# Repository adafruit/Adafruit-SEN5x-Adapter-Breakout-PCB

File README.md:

## Adafruit SEN54 or SEN55 Adapter Breakout - STEMMA QT / Qwiic PCB

<a href="http://www.adafruit.com/products/5964"><br/>
Click here to purchase one from the Adafruit shop</a>

PCB files for the Adafruit SEN54 or SEN55 Adapter Breakout - STEMMA QT / Qwiic. 

Format is EagleCAD schematic and board layout
* https://www.adafruit.com/product/5964

### Description

Now you can quickly integrate the Sensirion SEN54 / SEN55 environmental sensor node into your microcontroller or microcomputer project, with no soldering or fiddly breadboarding - thanks to this here Adafruit SEN54 or SEN55 Adapter Breakout. We covered the awesome Sensirion SEN54 / SEN55 environmental sensor nodes on EYE ON NPI a while ago, it's an awesome all-in-one air quality sensor, but has the annoyance that it requires 5V power and it has a special cable connection.

This adapter breakout will make an instant friendship with all SEN5x boards, thanks to a JST GH-compatible connector in the middle so that you can plug a 6-pin GH cable directly between your SEN and this adapter. In the middle is a small switch-cap boost converter that will generate 5V at 100mA to power the fan and electronics in the SEN5x even if you're using 3V power and logic. Then you can use any ol' STEMMA QT cable to plug into your Metro, Feather, QT Py, Raspberry Pi, etc etc. I2C port.

Once you've got it plugged together, you can run Sensirion's Arduino library or Raspberry Pi Python library to read temperature, humidity, VOC, Particulate Matter PM1 / PM2.5 / PM4 and PM10. (NOx reading is also available on the SEN55)

Please note: this board does NOT come with a JST GH-compatible cable NOR a SEN5x sensor! You can pick up the cable here, and a SEN5x from DigiKey.

### License

Adafruit invests time and resources providing this open source design, please support Adafruit and open-source hardware by purchasing products from [Adafruit](https://www.adafruit.com)!

Designed by Limor Fried/Ladyada for Adafruit Industries.

Creative Commons Attribution/Share-Alike, all text above must be included in any redistribution. 
See license.txt for additional details.

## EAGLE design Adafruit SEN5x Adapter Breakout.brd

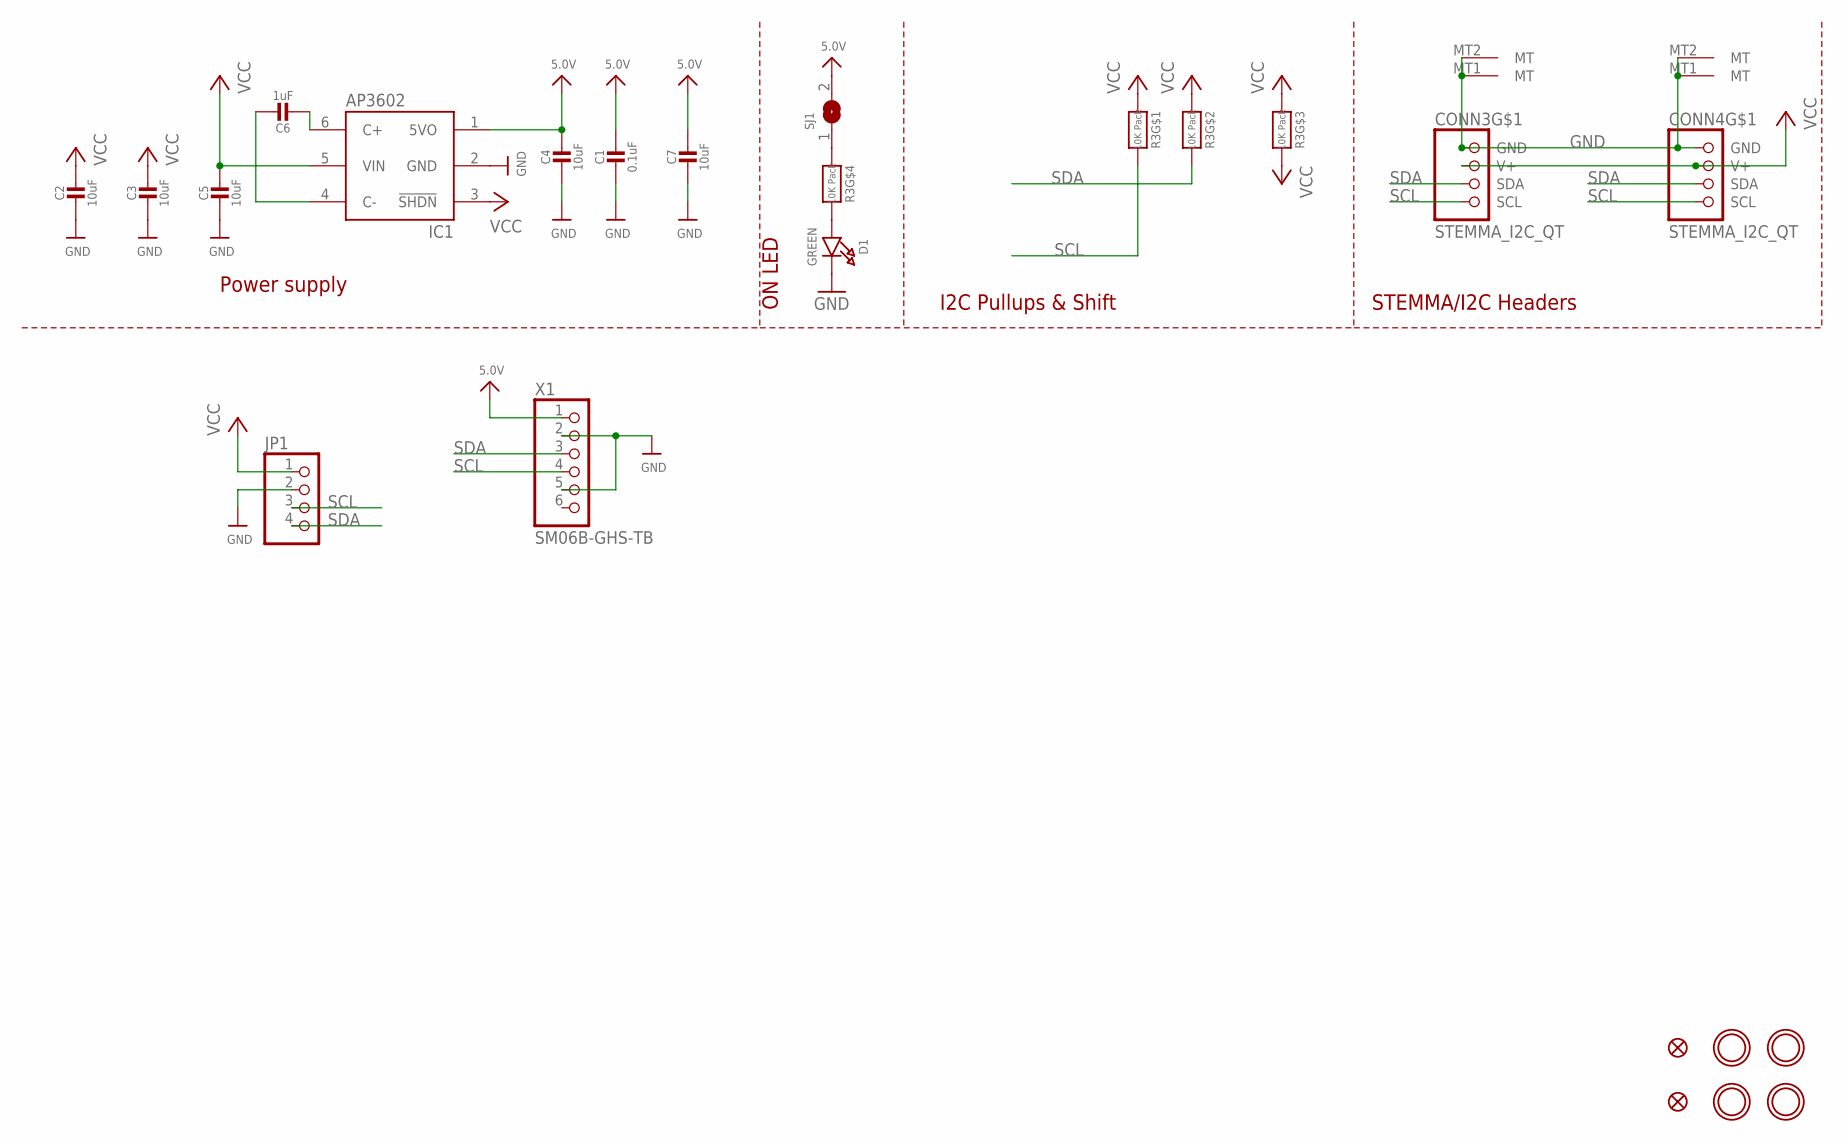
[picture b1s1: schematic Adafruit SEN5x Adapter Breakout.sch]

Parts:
C1: 0.1uF; 0603-NO
C2, C3, C4, C5, C7: 10uF; 0805-NO
C6: 1uF; 0805-NO
CONN3, CONN4: STEMMA_I2C_QT; JST_SH4
D1: GREEN; CHIPLED_0603_NOOUTLINE
FID3, FID4: FIDUCIAL_1MM
IC1: AP3602/RT9361; SOT23-6
JP1: HEADER-1X4ROUND; 1X04_ROUND
R3: 10K Pack; RESPACK_4X0603
SJ1: SOLDERJUMPERCLOSED; SOLDERJUMPER_CLOSEDWIRE
U$1, U$17, U$19, U$21: MOUNTINGHOLE2.5; MOUNTINGHOLE_2.5_PLATED
X1: SM06B-GHS-TB; CONN_SM06B-GHS-TB_JST

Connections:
5.0V: C1.1, C4.1, C7.1, IC1.1 (5VO), SJ1.2, X1.1
GND: C1.2, C2.2, C3.2, C4.2, C5.2, C7.2, CONN3.1 (GND), CONN3.MT1 (MT), CONN3.MT2 (MT), CONN4.1 (GND), CONN4.MT1 (MT), CONN4.MT2 (MT), D1.C, IC1.2 (GND), JP1.2, X1.2, X1.5
unnamed: D1.A, R3.5 (2)
unnamed: R3.4 (1), SJ1.1
unnamed: C6.2, IC1.6 (C+)
unnamed: C6.1, IC1.4 (C-)
SCL: CONN3.4 (SCL), CONN4.4 (SCL), JP1.3, R3.8 (2), X1.4
SDA: CONN3.3 (SDA), CONN4.3 (SDA), JP1.4, R3.7 (2), X1.3
VCC: C2.1, C3.1, C5.1, CONN3.2 (V+), CONN4.2 (V+), IC1.3 (!SHDN), IC1.5 (VIN), JP1.1, R3.1, R3.2 (1), R3.3 (1), R3.6 (2)

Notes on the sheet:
I2C Pullups & Shift
STEMMA/I2C Headers
ON LED
Power supply

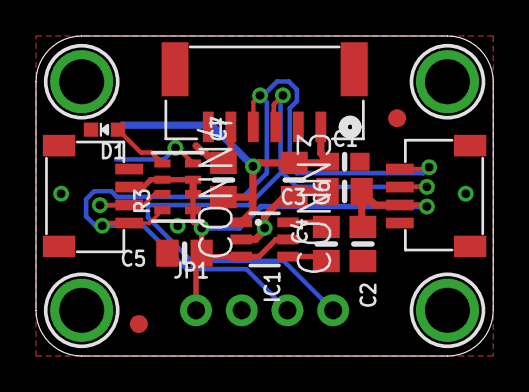
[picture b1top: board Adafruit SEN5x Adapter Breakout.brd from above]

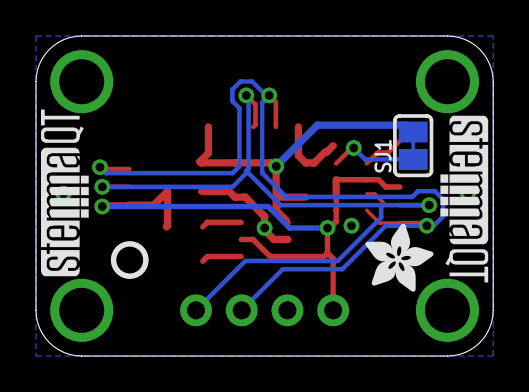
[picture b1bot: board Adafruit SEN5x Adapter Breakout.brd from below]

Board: 2 copper layers, 25.4 x 17.8 mm, 35 parts (8 on the bottom side), 9 nets.

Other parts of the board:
PLABEL5: PLABEL5
PLABEL13: PLABEL13
PLABEL14: PLABEL14
PLABEL15: PLABEL15
PLABEL16: PLABEL16
PLABEL17: PLABEL17
PLABEL18: PLABEL18
PLABEL19: PLABEL19
PLABEL20: PLABEL20
PLABEL21: PLABEL21
U$15: ADAFRUIT_3.5MM
U$25: PCBFEAT-REV-040
U$30, U$31: STEMMAQT

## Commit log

2024-05-13 cookiecutter

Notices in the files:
parts and their libraries:
microbuilder: This work is placed in the public domain, and may be freely used for commercial and non-commercial work with the following conditions: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
